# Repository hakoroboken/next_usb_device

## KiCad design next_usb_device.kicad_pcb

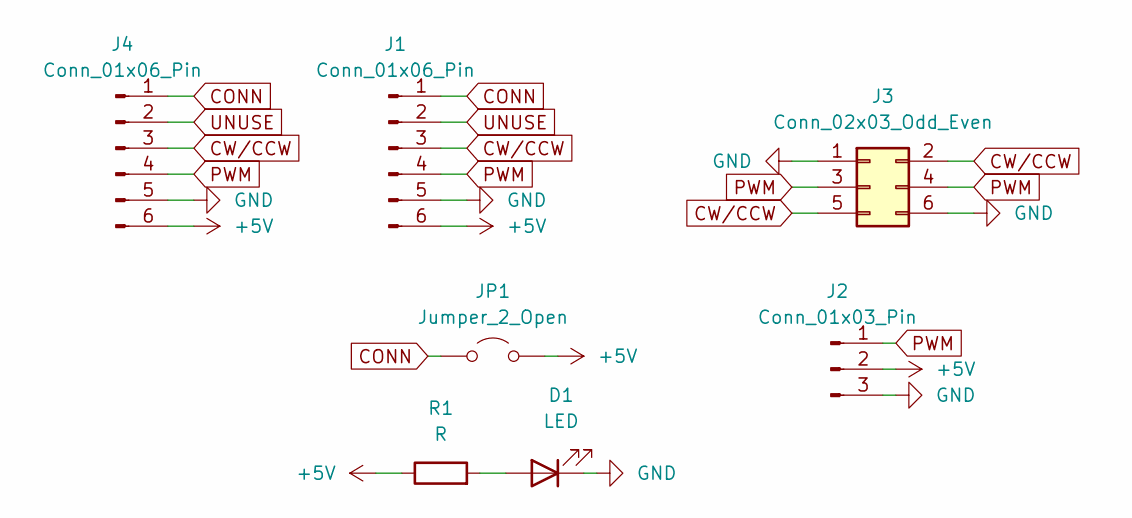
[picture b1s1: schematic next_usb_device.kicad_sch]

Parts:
D1: LED; LED_D3.0mm
J1, J4: Conn_01x06_Pin; PinSocket_1x06_P2.54mm_Vertical
J2: Conn_01x03_Pin; PinSocket_1x03_P2.54mm_Vertical
J3: Conn_02x03_Odd_Even; PinSocket_2x03_P2.54mm_Horizontal
JP1: Jumper_2_Open; SolderJumper-2_P1.3mm_Open_RoundedPad1.0x1.5mm
R1: R; R_Axial_DIN0207_L6.3mm_D2.5mm_P10.16mm_Horizontal

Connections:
+5V: J1.6, J2.2, J4.6, JP1.2 (B), R1.1
CONN: J1.1, J4.1, JP1.1 (A)
CW/CCW: J1.3, J3.2, J3.5, J4.3
GND: D1.1 (K), J1.5, J2.3, J3.1, J3.6, J4.5
unnamed: D1.2 (A), R1.2
PWM: J1.4, J2.1, J3.3, J3.4, J4.4
UNUSE: J1.2, J4.2

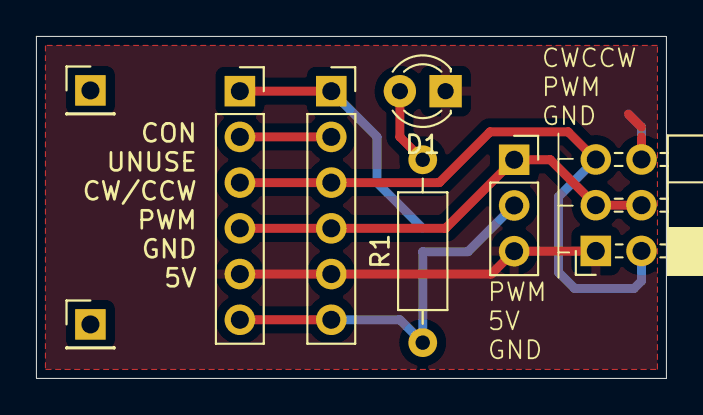
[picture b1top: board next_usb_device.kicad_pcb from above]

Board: 2 copper layers, 35.0 x 19.0 mm, 7 parts (1 on the bottom side), 7 nets.
